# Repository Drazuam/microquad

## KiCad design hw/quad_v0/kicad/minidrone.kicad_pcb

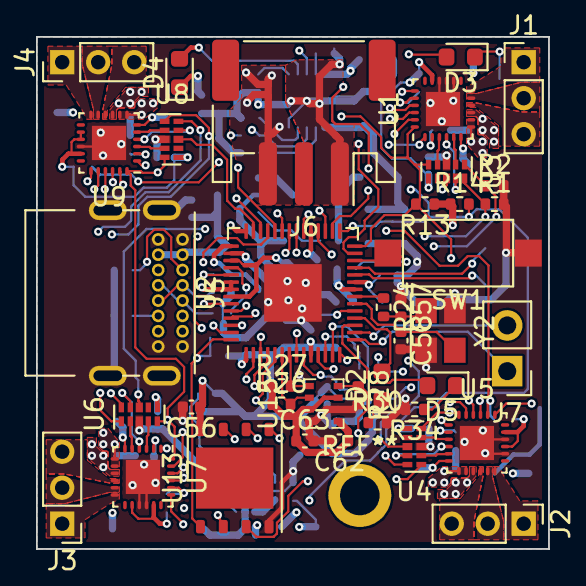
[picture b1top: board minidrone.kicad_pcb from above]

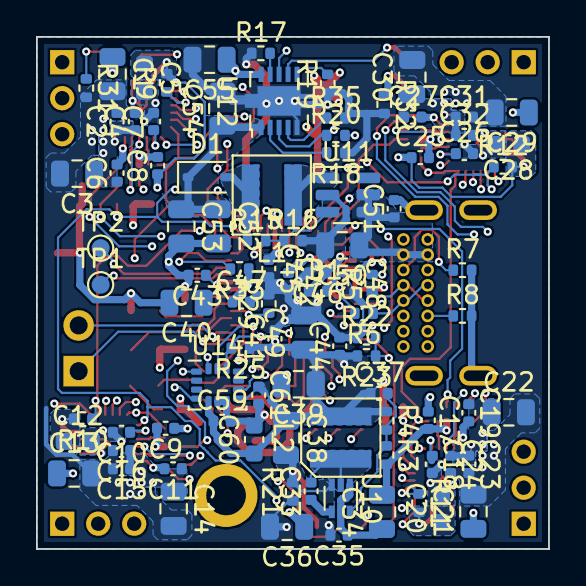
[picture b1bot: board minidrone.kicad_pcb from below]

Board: 4 copper layers, 28.4 x 28.4 mm, 132 parts (93 on the bottom side), 109 nets.

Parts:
C1, C3, C13, C14, C21, C22, C29, C30, C34, C36, C38, C39, C40, C49, C50, C52, C53, C54, C55: 10uF; C_0805_2012Metric
C2, C4, C6, C7, C8, C9, C10, C11, C15, C16, C17, C18, C19, C23, C24, C25, C26, C27, C31, C32, C33, C35, C41, C42, C43, C44, C45, C46, C47, C48, C51, C56, C59, C61, C62, C63: 0.1uF; C_0402_1005Metric
C5, C12, C20, C28, C60: 4.7uF; C_0603_1608Metric
C37: DNP; C_0402_1005Metric
C57, C58: 30pF; C_0402_1005Metric
D1: 20V, 1A; D_SOD-323
D2, D3, D4, D5: GREEN; LED_0603_1608Metric
FB1: 30 Ohm; R_0402_1005Metric
J1, J2, J3, J4: Motor; PinHeader_1x03_P2.00mm_Vertical
J5: USB_C; USB_C_Receptacle_CVILUX
J6: Battery; JST_PH_S3B-PH-SM4-TB_1x03-1MP_P2.00mm_Horizontal
J7: Conn_01x02_Pin; PinHeader_1x02_P2.54mm_Vertical
L1, L2: 4.7uH; EXLA1V04
R1, R2, R3, R9, R10, R11, R12, R13, R14, R16, R20, R25, R26, R27, R28, R30, R31, R32, R33, R34, R35: 10K; R_0402_1005Metric
R4: 31K; R_0402_1005Metric
R5, R6: 27.4; R_0402_1005Metric
R7, R8: 5.1K; R_0402_1005Metric
R15: 115K; R_0402_1005Metric
R17: 3.6K; R_0402_1005Metric
R18: 375; R_0402_1005Metric
R19: 100K; R_0402_1005Metric
R21: 0; R_0402_1005Metric
R22, R23, R29: DNP; R_0402_1005Metric
R24: 1K; R_0402_1005Metric
SW1: SW_DIP_x01; SW_SPST_CK_RS282G05A3
TP1, TP2: TestPoint; TestPoint_Pad_D1.0mm
U1, U5, U7, U9: DRV8311P; QFN-24_EP_3x3_Pitch0.4mm
U2: RP2040; QFN-56-1EP_7x7mm_P0.4mm_EP3.2x3.2mm
U3, U4, U6, U8: USON-10_2.5x1.0mm_P0.5mm
U10: TPS563207S; SOT-563
U11: TLV61048; SOT-23-6
U12: BQ25171-Q1; VSON-10-1EP_3x3mm_P0.5mm_EP1.65x2.4mm
U13: 128MBIT; WSON-8-1EP_6x5mm_P1.27mm_EP3.4x4.3mm
U14: ICM-42670-P; LGA-14_3x2.5mm_P0.5mm_LayoutBorder3x4y
U15: DPS310XTSA1; Bosch_LGA-8_2x2.5mm_P0.65mm_ClockwisePinNumbering
Y2: 12MHz; Crystal_SMD_Abracon_ABM8AIG-4Pin_3.2x2.5mm

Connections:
+1V1: C40.1, C42.1, C43.1, U2.23 (DVDD), U2.45 (VREG_VOUT), U2.50 (DVDD)
+BATT: C1.1, C2.1, C3.1, C4.1, C6.1, C11.1, C13.1, C14.1, C15.1, C16.1, C19.1, C21.1, C22.1, C23.1, C24.1, C27.1, C29.1, C30.1, C31.1, C32.1, C34.1, C35.1, C36.1, C55.1, J6.3, U1.7 (VIN_AVDD), U1.8 (VM), U5.7 (VIN_AVDD), U5.8 (VM), U7.7 (VIN_AVDD), U7.8 (VM), U9.7 (VIN_AVDD), U9.8 (VM), U10.1 (VIN), U10.5 (EN), U12.10 (OUT)
/BARO_INT: R28.1, U2.3 (GPIO1), U15.5 (SDO/INT)
/BARO_SCL: R27.2, U2.7 (GPIO5), U15.4 (SCK/SCL)
/BARO_SDA: R26.2, U2.6 (GPIO4), U15.3 (SDI/SDA)
/CE_N: R20.1, U2.27 (GPIO16), U12.3 (CE_N)
/FAULT_N: R14.2, U1.1 (FAULT_N), U2.29 (GPIO18), U5.1 (FAULT_N), U7.1 (FAULT_N), U9.1 (FAULT_N)
/IMU_CS_N: R25.2, U2.12 (GPIO9), U14.12 (CS)
/IMU_INT1: U2.8 (GPIO6), U14.4 (INT1)
/IMU_INT2: U2.9 (GPIO7), U14.9 (INT2)
/IMU_SCLK: U2.13 (GPIO10), U14.13 (SCLK)
/IMU_SDI: U2.14 (GPIO11), U14.14 (SDI)
/IMU_SDO: U2.11 (GPIO8), U14.1 (SDO)
/MC1_CS_N: R9.1, U1.20 (SCS_N), U2.30 (GPIO19)
/MC1_SENSE: U2.38 (GPIO26_ADC0), U3.8 (D)
/MC2_CS_N: R10.1, U2.31 (GPIO20), U5.20 (SCS_N)
/MC2_SENSE: U2.39 (GPIO27_ADC1), U4.8 (D)
/MC3_CS_N: R11.1, U2.32 (GPIO21), U7.20 (SCS_N)
/MC3_SENSE: U2.40 (GPIO28_ADC2), U6.8 (D)
/MC4_CS_N: R12.1, U2.34 (GPIO22), U9.20 (SCS_N)
/MC4_SENSE: U2.41 (GPIO29_ADC3), U8.8 (D)
/MC_SCLK: U1.23 (SCLK), U2.4 (GPIO2), U5.23 (SCLK), U7.23 (SCLK), U9.23 (SCLK)
/MC_SDI: U1.22 (SDI), U2.5 (GPIO3), U5.22 (SDI), U7.22 (SDI), U9.22 (SDI)
/MC_SDO: U1.21 (SDO), U2.2 (GPIO0), U5.21 (SDO), U7.21 (SDO), U9.21 (SDO)
/Motor Controller 1/AVDD: C5.1, C8.1, R9.2, U1.17 (AVDD), U3.6 (VDD)
/Motor Controller 2/AVDD: C9.1, C12.1, R10.2, U4.6 (VDD), U5.15 (AD0), U5.17 (AVDD)
/Motor Controller 3/AVDD: C17.1, C20.1, R11.2, U6.6 (VDD), U7.14 (AD1), U7.17 (AVDD)
/Motor Controller 4/AVDD: C25.1, C28.1, R12.2, U8.6 (VDD), U9.14 (AD1), U9.15 (AD0), U9.17 (AVDD)
/PWM_SYNC: U1.19 (PWM_SYNC), U2.35 (GPIO23), U5.19 (PWM_SYNC), U7.19 (PWM_SYNC), U9.19 (PWM_SYNC)
/QSPI_CS: R22.2, R23.1, U2.56 (QSPI_SS), U13.1 (CS_N)
/SENSE_SEL_0: R2.1, U2.36 (GPIO24), U3.1 (A0), U4.1 (A0), U6.1 (A0), U8.1 (A0)
/SENSE_SEL_1: R1.1, U2.37 (GPIO25), U3.10 (A1), U4.10 (A1), U6.10 (A1), U8.10 (A1)
/SLEEP_N: R13.2, U1.24 (SLEEP_N), U2.28 (GPIO17), U3.5 (EN), U4.5 (EN), U5.24 (SLEEP_N), U6.5 (EN), U7.24 (SLEEP_N), U8.5 (EN), U9.24 (SLEEP_N)
/UART0_RX: J7.2, U2.16 (GPIO13)
/UART0_TX: J7.1, U2.15 (GPIO12)
Earth: C1.2, C2.2, C3.2, C4.2, C13.2, C14.2, C15.2, C16.2, C21.2, C22.2, C23.2, C24.2, C29.2, C30.2, C31.2, C32.2, C35.2, C36.2, C54.2, C55.2, J6.1, R17.1, R18.1, R19.1, R21.1, R31.2, R32.2, R35.2, U1.9 (PGND), U5.9 (PGND), U7.9 (PGND), U9.9 (PGND), U12.5 (GND), U12.11 (EP)
GNDA: C5.2, C7.2, C8.2, C9.2, C10.2, C12.2, C17.2, C18.2, C20.2, C25.2, C26.2, C28.2, C34.2, C38.2, C39.2, C40.2, C41.2, C42.2, C43.2, C44.2, C45.2, C46.2, C47.2, C48.2, C49.2, C50.2, C51.2, C52.2, C53.2, C56.2, C57.1, C58.2, C59.2, C60.2, C61.2, C62.2, C63.2, J5.A1 (GND), J5.A12 (GND), J5.B1 (GND), J5.B12 (GND), J5.S1 (SHIELD), R1.2, R2.2, R3.2, R7.2, R8.2, R16.2, R21.2, R22.1, R28.2, R29.2, R30.2, R34.2, SW1.1, U1.14 (AD1), U1.15 (AD0), U1.16 (AGND), U1.25 (EP), U2.57 (GND), U3.3 (GND), U4.3 (GND), U5.14 (AD1), U5.16 (AGND), U5.25 (EP), U6.3 (GND), U7.15 (AD0), U7.16 (AGND), U7.25 (EP), U8.3 (GND), U9.16 (AGND), U9.25 (EP), U10.3 (GND), U11.2 (GND), U13.4 (GND), U14.6 (GND), U14.7 (FSYNC), U15.1 (GND), U15.7 (GND), Y2.2, Y2.4
unnamed: C57.2, R24.2, Y2.1
unnamed: D1.2 (A), L1.2, R15.1
unnamed: C52.1, C53.1, C54.1, D1.1 (K), U12.1 (IN)
unnamed: D2.2 (A), U2.18 (GPIO15)
unnamed: D2.1 (K), R30.1
unnamed: D3.2 (A), U12.8 (STAT2)
unnamed: D3.1 (K), R31.1
unnamed: D4.2 (A), U12.7 (STAT1)
unnamed: D4.1 (K), R32.1
unnamed: D5.2 (A), U2.17 (GPIO14)
unnamed: D5.1 (K), R34.1
unnamed: J1.1, U1.12 (OUTC)
unnamed: J1.2, U1.11 (OUTB)
unnamed: J1.3, U1.10 (OUTA)
unnamed: J2.1, U5.12 (OUTC)
unnamed: J2.2, U5.11 (OUTB)
unnamed: J2.3, U5.10 (OUTA)
unnamed: J3.1, U7.12 (OUTC)
unnamed: J3.2, U7.11 (OUTB)
unnamed: J3.3, U7.10 (OUTA)
unnamed: J4.1, U9.12 (OUTC)
unnamed: J4.2, U9.11 (OUTB)
unnamed: J4.3, U9.10 (OUTA)
unnamed: J5.A5 (CC1), R7.1
unnamed: J5.B5 (CC2), R8.1
unnamed: J5.A6 (D+), J5.B6 (D+), R5.1
unnamed: J5.A7 (D-), J5.B7 (D-), R6.1
unnamed: C6.2, U1.6 (CP)
unnamed: C7.1, U1.2 (CSAREF)
unnamed: U1.5 (SOA), U3.2 (S1)
unnamed: U1.4 (SOB), U3.9 (S2)
unnamed: U1.3 (SOC), U3.4 (S3)
unnamed: C48.1, FB1.2, U2.43 (ADC_AVDD)
unnamed: R33.2, SW1.2, U2.26 (RUN)
unnamed: TP1.1, U2.24 (SWCLK)
unnamed: TP2.1, U2.25 (SWD)
unnamed: R29.1, U2.19 (TESTEN)
unnamed: R6.2, U2.46 (USB_DM)
unnamed: R5.2, U2.47 (USB_DP)
unnamed: C58.1, U2.20 (XIN), Y2.3
unnamed: R24.1, U2.21 (XOUT)
unnamed: U4.2 (S1), U5.5 (SOA)
unnamed: U4.9 (S2), U5.4 (SOB)
unnamed: U4.4 (S3), U5.3 (SOC)
unnamed: C11.2, U5.6 (CP)
unnamed: C10.1, U5.2 (CSAREF)
unnamed: U6.2 (S1), U7.5 (SOA)
unnamed: U6.9 (S2), U7.4 (SOB)
unnamed: U6.4 (S3), U7.3 (SOC)
unnamed: C19.2, U7.6 (CP)
unnamed: C18.1, U7.2 (CSAREF)
unnamed: U8.2 (S1), U9.5 (SOA)
unnamed: U8.9 (S2), U9.4 (SOB)
unnamed: U8.4 (S3), U9.3 (SOC)
unnamed: C27.2, U9.6 (CP)
unnamed: C26.1, U9.2 (CSAREF)
unnamed: C33.1, U10.4 (BST)
unnamed: C37.2, R3.1, R4.2, U10.6 (FB)
unnamed: C33.2, L2.1, U10.2 (SW)
unnamed: R15.2, R16.1, U11.3 (FB)
unnamed: L1.1, U11.1 (SW)
unnamed: R19.2, U12.6 (CHM_TMR)
unnamed: R18.2, U12.2 (ISET)
unnamed: R35.1, U12.4 (TS)
unnamed: R17.2, U12.9 (VSET)
unnamed: U2.52 (QSPI_SCLK), U13.6 (CLK)
unnamed: U2.53 (QSPI_SD0), U13.5 (IO0)
unnamed: U2.55 (QSPI_SD1), U13.2 (IO1)
unnamed: U2.54 (QSPI_SD2), U13.3 (IO2)
unnamed: U2.51 (QSPI_SD3), U13.7 (IO3)
VBUS: C50.1, C51.1, J5.A4 (VBUS), J5.A9 (VBUS), J5.B4 (VBUS), J5.B9 (VBUS), U11.4 (EN), U11.5 (VIN)
VCC: C37.1, C38.1, C39.1, C41.1, C44.1, C45.1, C46.1, C47.1, C49.1, C56.1, C59.1, C60.1, C61.1, C62.1, C63.1, FB1.1, L2.2, R4.1, R13.1, R14.1, R20.2, R23.2, R25.1, R26.1, R27.1, R33.1, U2.1 (IOVDD), U2.10 (IOVDD), U2.22 (IOVDD), U2.33 (IOVDD), U2.42 (IOVDD), U2.44 (VREG_IN), U2.48 (USB_VDD), U2.49 (IOVDD), U13.8 (VCC), U14.5 (VDDIO), U14.8 (VDD), U15.2 (CSB/SEL), U15.6 (VDDIO), U15.8 (VDD)

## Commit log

2023-07-24 initial project share. v0 test bed schematic and layout ready
2023-07-28 adds ros2 node structure for a thrust publisher
